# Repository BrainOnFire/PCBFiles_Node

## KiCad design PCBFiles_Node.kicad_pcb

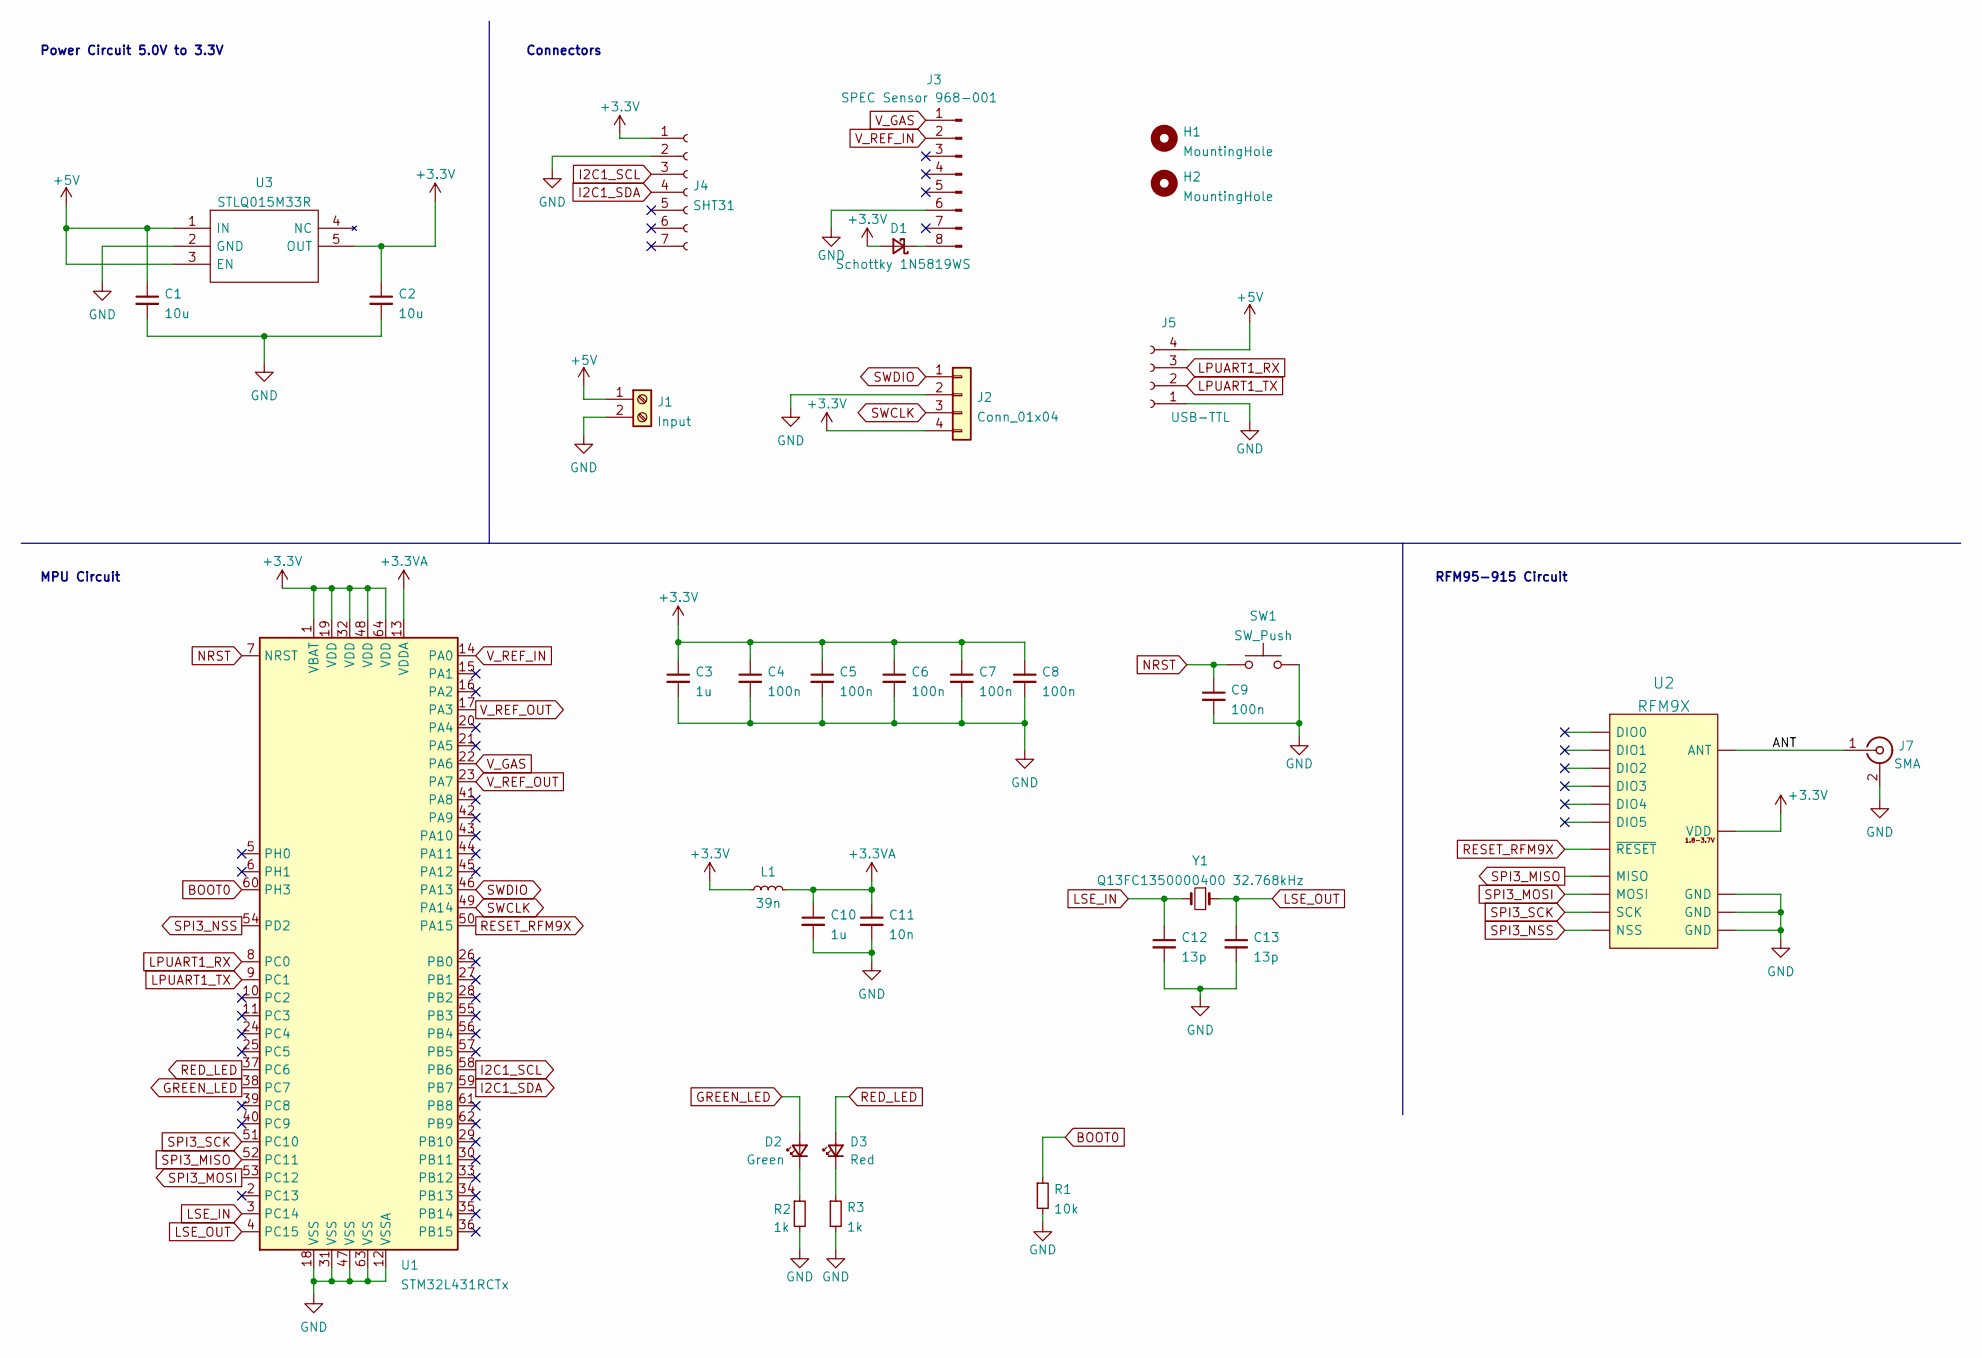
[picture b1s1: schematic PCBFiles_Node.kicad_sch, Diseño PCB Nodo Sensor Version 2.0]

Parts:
C1, C2: 10u; C_1206_3216Metric; LCSC Part # C13585
C3, C10: 1u; C_0402_1005Metric; LCSC Part # C52923
C4, C5, C6, C7, C8, C9: 100n; C_0402_1005Metric; LCSC Part # C307331
C11: 10n; C_0402_1005Metric; LCSC Part # C15195
C12, C13: 13p; C_0402_1005Metric; LCSC Part # C48936
D1: Schottky 1N5819WS; D_SOD-323; LCSC Part # C191023
D2: Green; LED_0603_1608Metric; LCSC Part # C118334
D3: Red; LED_0603_1608Metric; LCSC Part # C118330
H1, H2: MountingHole; MountingHole_2.2mm_M2_Pad
J1: Input; TerminalBlock_bornier-2_P5.08mm
J2: Conn_01x04; PinSocket_1x04_P2.54mm_Vertical
J3: SPEC Sensor 968-001; PinHeader_1x08_P2.54mm_Horizontal
J4: SHT31; PinSocket_1x07_P2.54mm_Vertical
J5: USB-TTL; PinSocket_1x04_P2.54mm_Horizontal
J7: SMA; SMA_Samtec_SMA-J-P-X-ST-EM1_EdgeMount
L1: 39n; L_0402_1005Metric; LCSC Part # C335623
R1: 10k; R_0402_1005Metric; LCSC Part # C25744
R2, R3: 1k; R_0603_1608Metric; LCSC Part # C21190
SW1: SW_Push; SW_SPST_B3U-1000P; LCSC Part # B3U-1000P
U1: STM32L431RCTx; LQFP-64_10x10mm_P0.5mm; LCSC Part # C92468
U2: RFM9X; RFM9X-SMD; LCSC Part # C2844473
U3: STLQ015M33R; SOT95P280X145-5N; Mouser Part Number 511-STLQ015M33R
Y1: Q13FC1350000400 32.768kHz; Q13FC1350000400; LCSC Part # C32346

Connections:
+3.3VA: C10.1, C11.1, L1.2, U1.13 (VDDA)
+3V3: C2.1, C3.1, C4.1, C5.1, C6.1, C7.1, C8.1, D1.2 (A), J2.4, J4.1, L1.1, U1.1 (VBAT), U1.19 (VDD), U1.32 (VDD), U1.48 (VDD), U1.64 (VDD), U2.12 (VDD), U3.5 (OUT)
+5V: C1.1, J1.1, J5.4, U3.1 (IN), U3.3 (EN)
/ANT: J7.1 (In), U2.16 (ANT)
BOOT0: R1.1, U1.60 (PH3)
GND: C1.2, C2.2, C3.2, C4.2, C5.2, C6.2, C7.2, C8.2, C9.2, C10.2, C11.2, C12.2, C13.2, J1.2, J2.2, J3.6, J4.2, J5.1, J7.2 (Ext), R1.2, R2.2, R3.2, SW1.2, U1.12 (VSSA), U1.18 (VSS), U1.31 (VSS), U1.47 (VSS), U1.63 (VSS), U2.1 (GND), U2.8 (GND), U2.15 (GND), U3.2 (GND)
GREEN_LED: D2.2 (A), U1.38 (PC7)
I2C1_SCL: J4.3, U1.58 (PB6)
I2C1_SDA: J4.4, U1.59 (PB7)
LPUART1_RX: J5.3, U1.8 (PC0)
LPUART1_TX: J5.2, U1.9 (PC1)
LSE_IN: C12.1, U1.3 (PC14), Y1.2
LSE_OUT: C13.1, U1.4 (PC15), Y1.1
NRST: C9.1, SW1.1, U1.7 (NRST)
unnamed: D1.1 (K), J3.8
unnamed: D2.1 (K), R2.1
unnamed: D3.1 (K), R3.1
RED_LED: D3.2 (A), U1.37 (PC6)
RESET_RFM9X: U1.50 (PA15), U2.6 (~RESET)
SPI3_MISO: U1.52 (PC11), U2.2 (MISO)
SPI3_MOSI: U1.53 (PC12), U2.3 (MOSI)
SPI3_NSS: U1.54 (PD2), U2.5 (NSS)
SPI3_SCK: U1.51 (PC10), U2.4 (SCK)
SWCLK: J2.3, U1.49 (PA14)
SWDIO: J2.1, U1.46 (PA13)
V_GAS: J3.1, U1.22 (PA6)
V_REF_IN: J3.2, U1.14 (PA0)
V_REF_OUT: U1.17 (PA3), U1.23 (PA7)

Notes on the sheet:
RFM95-915 Circuit
MPU Circuit
Connectors
Power Circuit 5.0V to 3.3V

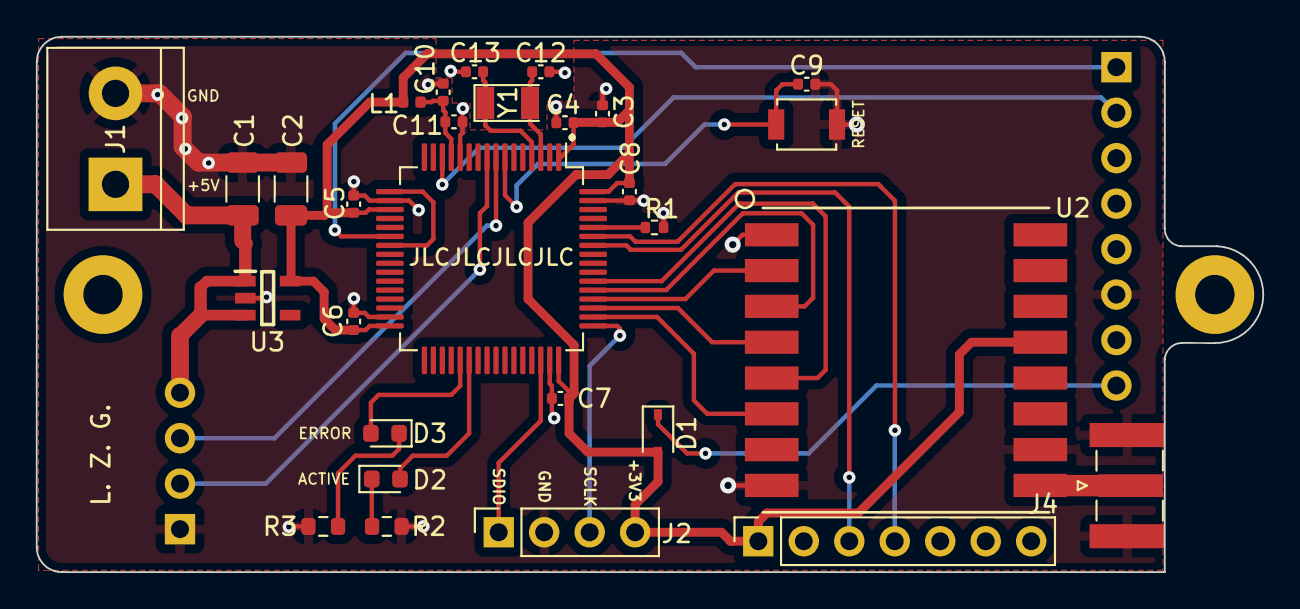
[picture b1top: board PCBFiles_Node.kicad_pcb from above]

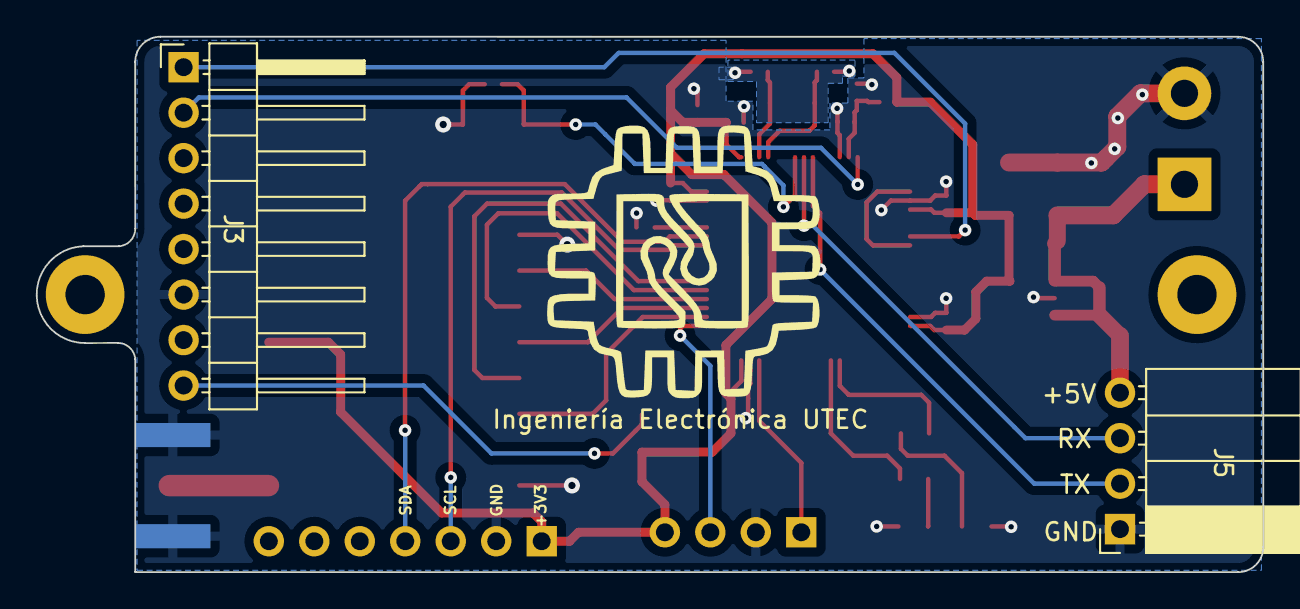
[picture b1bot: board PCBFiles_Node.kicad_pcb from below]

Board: 2 copper layers, 68.5 x 29.9 mm, 33 parts (2 on the bottom side), 28 nets.

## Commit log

2022-09-12 Added files to first commit
2022-09-12 Prueba de push nro. 2
2022-09-12 Prueba push Nro.3
2022-09-13 Prueba 3
2022-09-13 Prueba 4
2022-09-14 Trash files
2022-09-14 STM32 IC
2022-09-14 Backup
2022-09-17 Block Diagram
2022-09-20 Voltage regulator, Crystal, RFM9x, base settings
2022-09-22 Connectors, MPU Circuit & Pins Schematic Update
2022-09-26 First PCB Design
2022-09-30 Replaced STM32L432KCU6 for STM32L431RCTx in Schematic and PCB
2022-10-02 First routing
2022-10-05 Minor changes
2022-10-14 Gerber and Fab files
2022-11-02 Backups
2022-12-01 Via Parameters Changed
